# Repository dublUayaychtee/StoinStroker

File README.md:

# StoinStroker

This repo contains all the firmware and hardware for the StoinStroker.

If you're looking for the latest docs/builds, see our [Releases Page](https://github.com/dublUayaychtee/StenoStroker/releases).

# Getting Started

First, clone this repo (and optionally checkout a branch)

```shell
git clone https://github.com/dublUayaychtee/StoinStroker.git
cd StoinStroker
```

# Init Submodules

Some libraries and resources are included as submodules, run the following
command to initialize them before opening the main sch

(If you get a missing library error, make sure to do this)

```shell
git submodule update --init --recursive
```

## Project Layout

If you want to use this project template for yourself, you can find it [here!](https://github.com/KenwoodFox/Project-Template)

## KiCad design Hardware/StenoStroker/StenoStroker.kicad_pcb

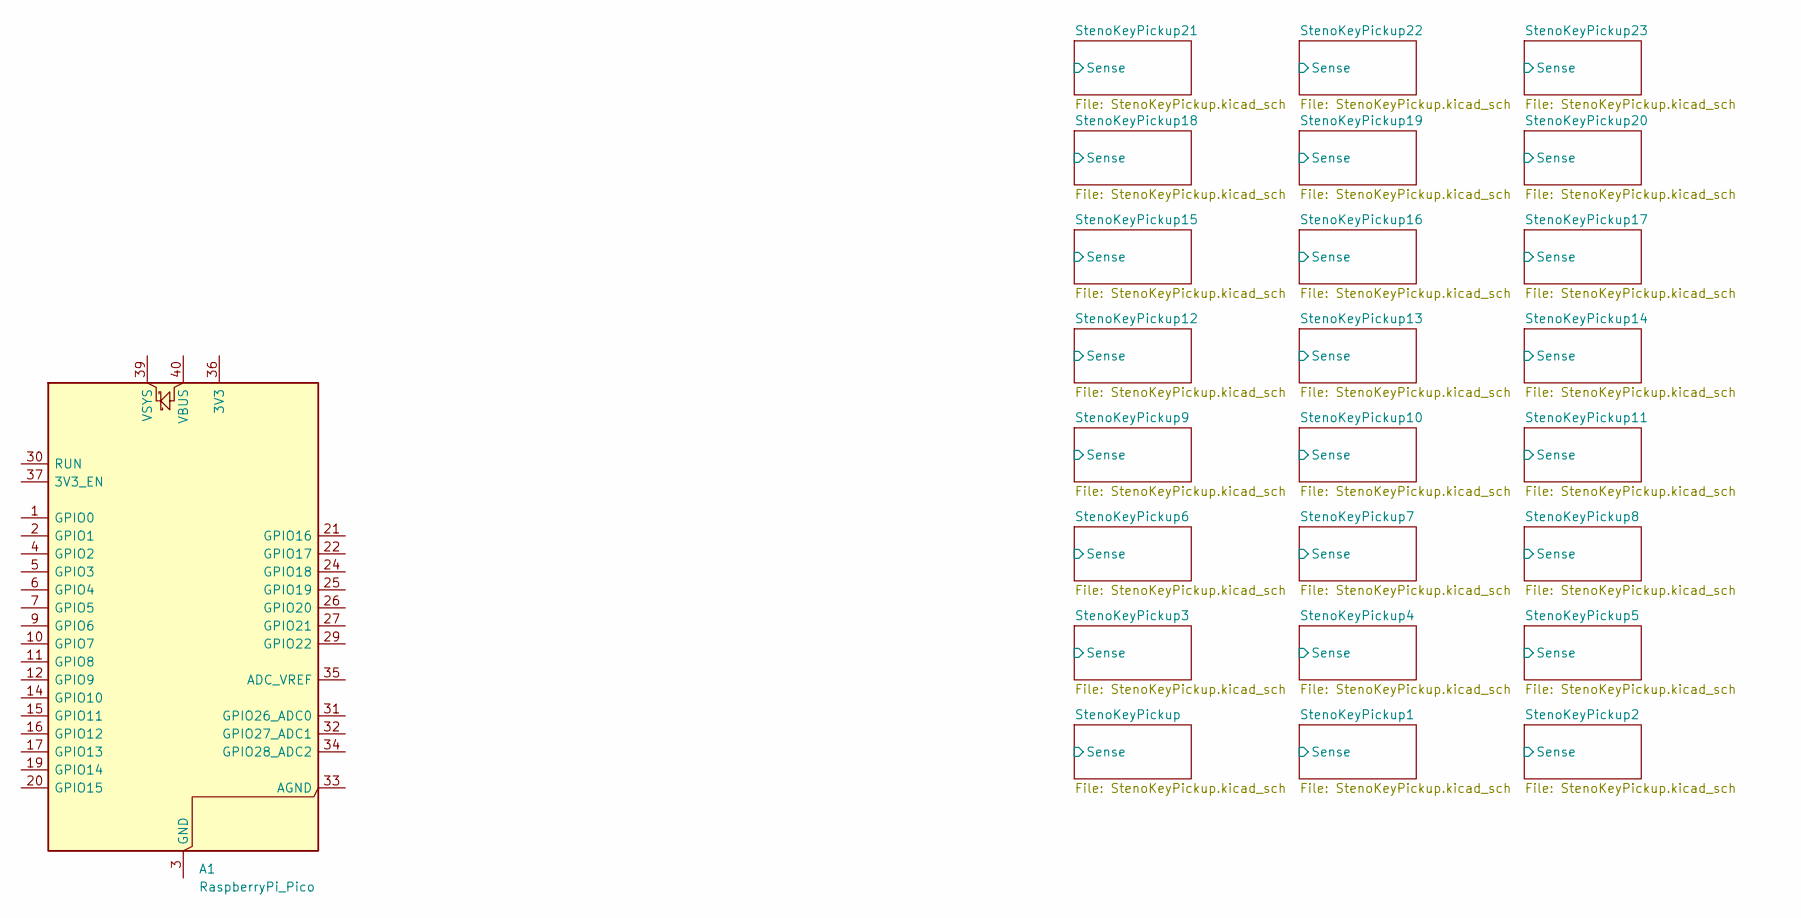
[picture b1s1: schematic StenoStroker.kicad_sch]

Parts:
A1: RaspberryPi_Pico; RaspberryPi_Pico_Common_SMD

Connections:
unnamed: A1.3 (GND), A1.8 (GND), A1.13 (GND), A1.18 (GND), A1.23 (GND), A1.28 (GND), A1.38 (GND)

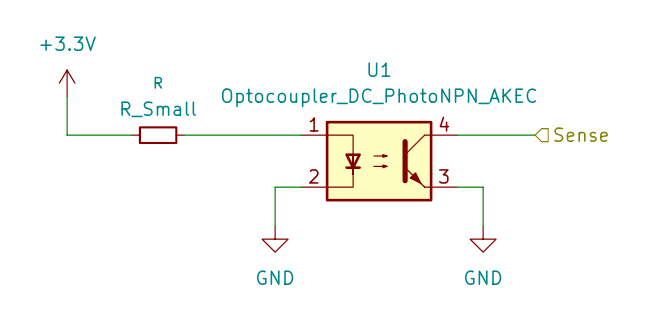
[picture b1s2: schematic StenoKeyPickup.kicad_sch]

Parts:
R: R_Small; R_0805_2012Metric
U1: Optocoupler_DC_PhotoNPN_AKEC

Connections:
unnamed: U1.2, U1.3

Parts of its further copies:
R2, R3, R4, R5, R6, R7, R8, R9, R10, R11, R12, R13, R14, R15, R16, R17, R18, R19, R20, R21, R22, R23, R24: R_Small; R_0805_2012Metric

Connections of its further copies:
+3.3V: R2.1, R3.1, R4.1, R5.1, R6.1, R7.1, R8.1, R9.1, R10.1, R11.1, R12.1, R13.1, R14.1, R15.1, R16.1, R17.1, R18.1, R19.1, R20.1, R21.1, R22.1, R23.1, R24.1; also elsewhere on the board

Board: 2 copper layers, 25 parts (0 on the bottom side), 2 nets, no tracks yet.

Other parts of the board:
R1: R_Small; R_0805_2012Metric

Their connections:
+3.3V: R1.1; also elsewhere on the board

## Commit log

2025-08-08 init
2025-08-08 Amazing work for rn
2025-08-08 make the repo correct
